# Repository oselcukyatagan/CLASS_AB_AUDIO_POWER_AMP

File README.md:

# CLASS_AB_AUDIO_POWER_AMP

This is the repository for the developing of the class AB audio power amplifier device. 

The repository contains the LTspice and KiCad files along with screenshots of the schematics and simulation results.

Used the technique of making a non polarized cap from 2 polarized electrolytic capacitors. to get the same capacitance, use 2 capacitors thats double the capacitance.

Vbe multiplier and the output stage transistors should be on the same heatsink for thermal considerations.

Ensured the isolated clean ground and dirty ground paths only intersect at a single point at the main power supply socket to prevent ground loops.

Adjust the vbe multiplier trimpot before initial power-on to prevent thermal runaway. calibrated quiescent current only after letting the amplifier idle to reach operating temperature.

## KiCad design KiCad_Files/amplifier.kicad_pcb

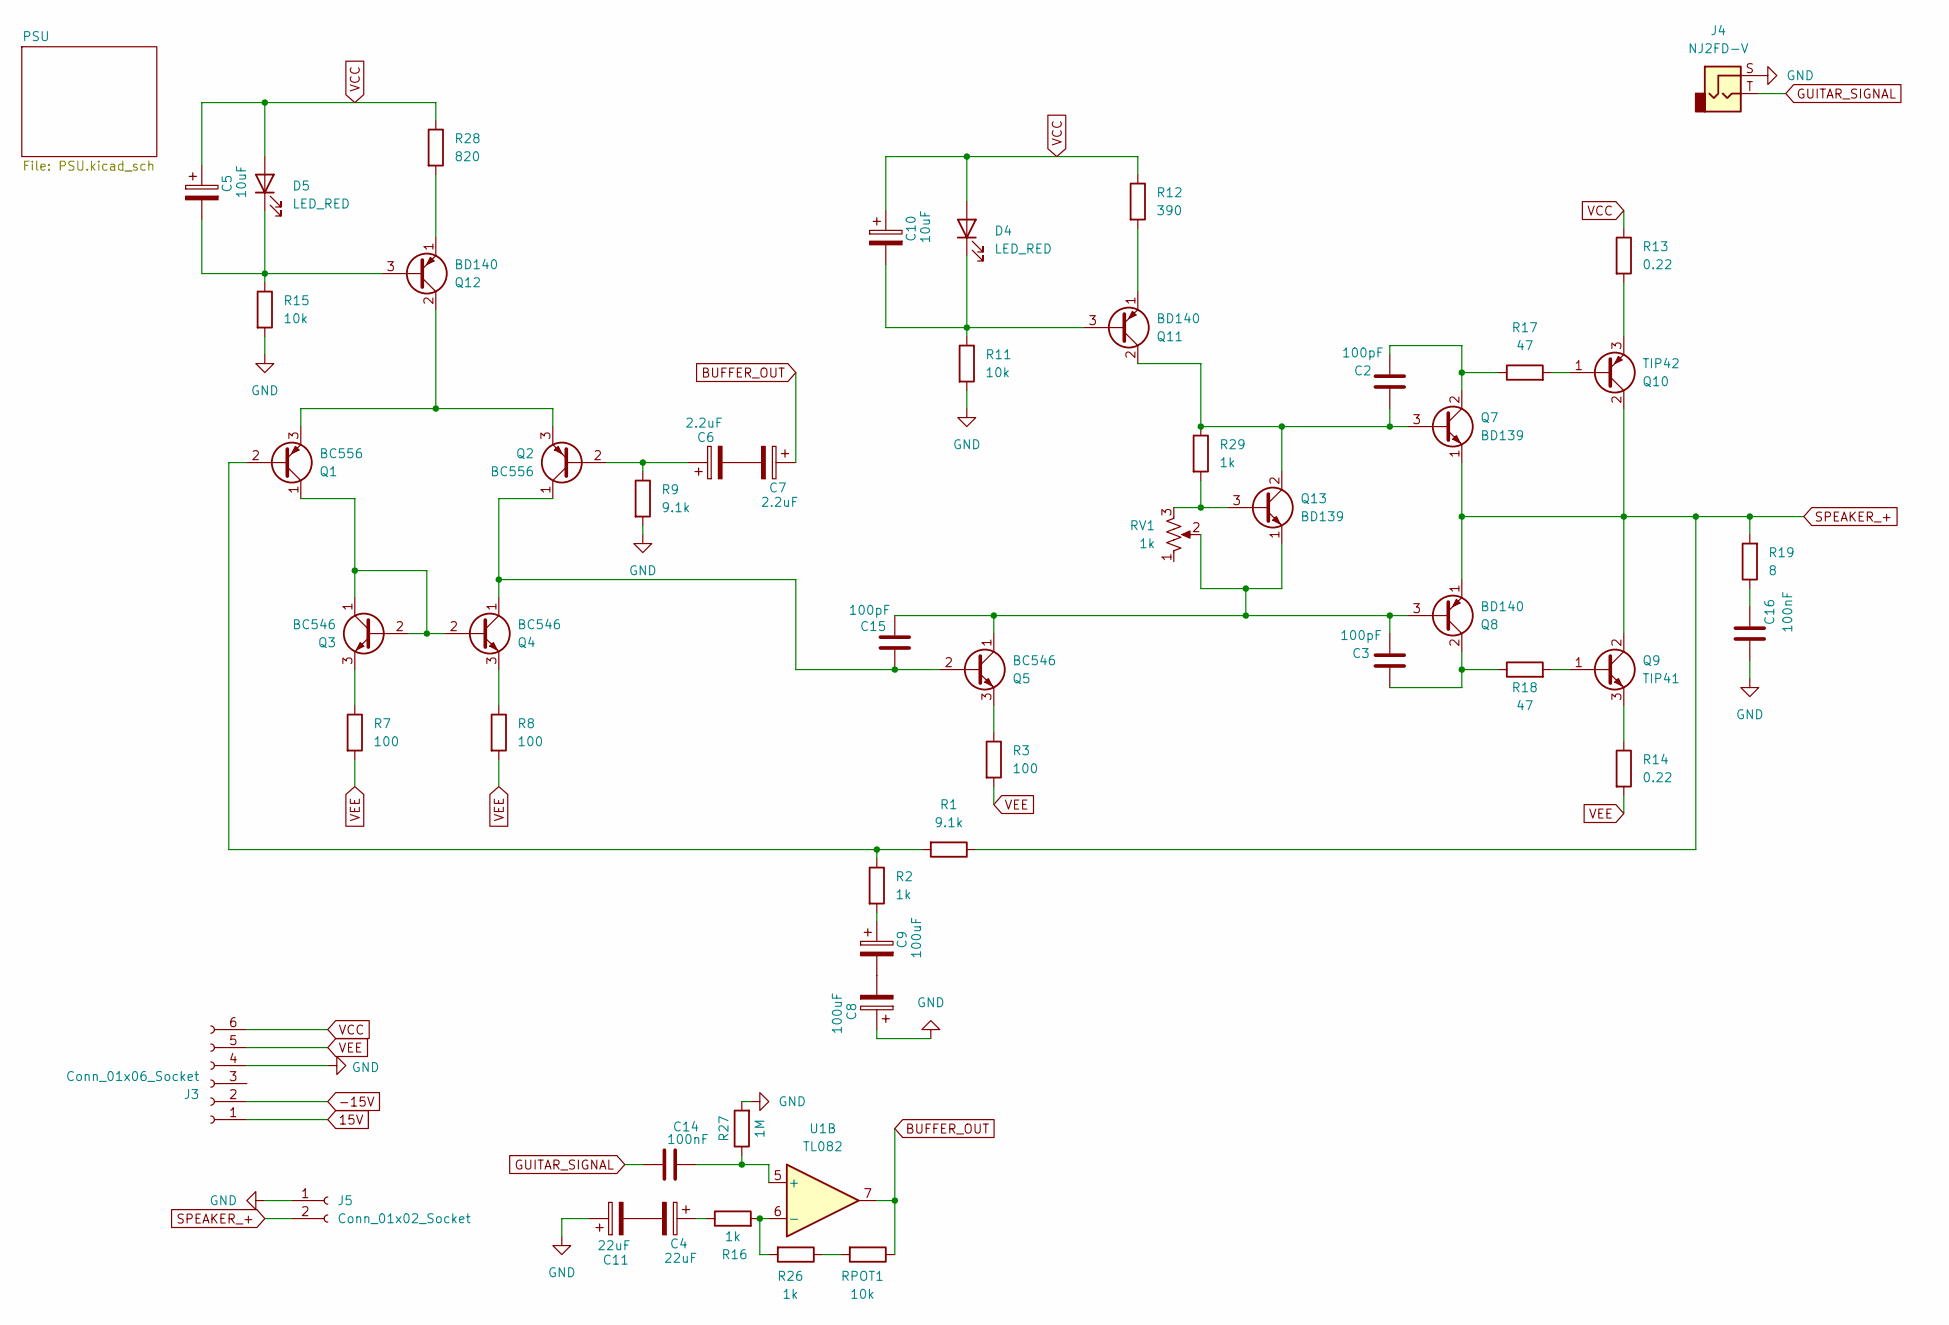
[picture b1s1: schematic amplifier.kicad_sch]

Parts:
C2, C3, C15: 100pF; C_Disc_D5.0mm_W2.5mm_P2.50mm
C4, C11: 22uF; CP_Radial_D8.0mm_P5.00mm
C5, C10: 10uF; CP_Radial_D8.0mm_P5.00mm
C6, C7: 2.2uF; CP_Radial_D8.0mm_P5.00mm
C8, C9: 100uF; CP_Radial_D8.0mm_P5.00mm
C14, C16: 100nF; C_Disc_D5.0mm_W2.5mm_P2.50mm
D4, D5: LED_RED; LED_D4.0mm
J3: Conn_01x06_Socket; TerminalBlock_Phoenix_MKDS-1,5-6-5.08_1x06_P5.08mm_Horizont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
J4: NJ2FD-V; Jack_3.5mm_CUI_SJ-3523-SMT_Horizontal
J5: Conn_01x02_Socket; TerminalBlock_Phoenix_MKDS-1,5-2-5.08_1x02_P5.08mm_Horizont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
Q1, Q2: BC556; TO-92_Inline
Q3, Q4, Q5: BC546; TO-92_Inline
Q7, Q13: BD139; TO-126-3_Vertical
Q8, Q11, Q12: BD140; TO-126-3_Vertical
Q9: TIP41; TO-220-3_Vertical
Q10: TIP42; TO-220-3_Vertical
R1, R9: 9.1k; R_Axial_DIN0207_L6.3mm_D2.5mm_P10.16mm_Horizontal
R2, R16, R26, R29: 1k; R_Axial_DIN0207_L6.3mm_D2.5mm_P10.16mm_Horizontal
R3, R7, R8: 100; R_Axial_DIN0207_L6.3mm_D2.5mm_P10.16mm_Horizontal
R11, R15: 10k; R_Axial_DIN0207_L6.3mm_D2.5mm_P10.16mm_Horizontal
R12: 390; R_Axial_DIN0207_L6.3mm_D2.5mm_P10.16mm_Horizontal
R13, R14: 0.22; R_Axial_DIN0207_L6.3mm_D2.5mm_P10.16mm_Horizontal
R17, R18: 47; R_Axial_DIN0207_L6.3mm_D2.5mm_P10.16mm_Horizontal
R19: 8; R_Axial_DIN0207_L6.3mm_D2.5mm_P10.16mm_Horizontal
R27: 1M; R_Axial_DIN0207_L6.3mm_D2.5mm_P10.16mm_Horizontal
R28: 820; R_Axial_DIN0207_L6.3mm_D2.5mm_P10.16mm_Horizontal
RPOT1: 10k; Potentiometer_ACP_CA6-H2,5_Horizontal
RV1: 1k; Potentiometer_ACP_CA6-H2,5_Horizontal
U1: TL082; DIP-8_W7.62mm

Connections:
15V: J3.1; also elsewhere on the board
-15V: J3.2; also elsewhere on the board
BUFFER_OUT: C7.1, RPOT1.1, U1.7
GUITAR_SIGNAL: C14.1, J4.T
unnamed: C4.1, R16.1
unnamed: C6.2, C7.2
unnamed: C8.2, C9.2
unnamed: C9.1, R2.2
unnamed: C4.2, C11.2
unnamed: C16.2, R19.1
unnamed: C10.2, D4.1 (K), Q11.3 (B), R11.1
unnamed: C5.2, D5.1 (K), Q12.3 (B), R15.1
unnamed: Q1.2 (B), R1.2, R2.1
unnamed: Q1.1 (C), Q3.1 (C), Q3.2 (B), Q4.2 (B)
unnamed 20: Q1.3 (E), Q2.3 (E), Q12.2 (C); also elsewhere on the board
unnamed: C6.1, Q2.2 (B), R9.1
unnamed: C15.1, Q2.1 (C), Q4.1 (C), Q5.2 (B)
unnamed: Q3.3 (E), R7.1
unnamed: Q4.3 (E), R8.1
unnamed: Q5.3 (E), R3.1
unnamed: C2.2, Q7.2 (C), R17.1
unnamed: C3.1, Q8.2 (C), R18.1
unnamed: Q9.1 (B), R18.2
unnamed: Q9.3 (E), R14.1
unnamed: Q10.1 (B), R17.2
unnamed: Q10.3 (E), R13.2
unnamed: C2.1, Q7.3 (B), Q11.2 (C), Q13.2 (C), R29.1
unnamed: Q11.1 (E), R12.2
unnamed: Q12.1 (E), R28.2
unnamed: Q13.3 (B), R29.2, RV1.3
unnamed: C3.2, C15.2, Q5.1 (C), Q8.3 (B), Q13.1 (E), RV1.2
unnamed: R26.1, RPOT1.2
unnamed: C14.2, R27.1, U1.5 (+)
unnamed: R16.2, R26.2, U1.6 (-)
SPEAKER_+: J5.2, Q7.1 (E), Q8.1 (E), Q9.2 (C), Q10.2 (C), R1.1, R19.2
TRANSFORMER_0V: C8.1, C11.1, C16.1, J3.4, J4.S, J5.1, R9.2, R11.2, R15.2, R27.2; also elsewhere on the board
VCC: C5.1, C10.1, D4.2 (A), D5.2 (A), J3.6, R12.1, R13.1, R28.1; also elsewhere on the board
VEE: J3.5, R3.2, R7.2, R8.2, R14.2; also elsewhere on the board

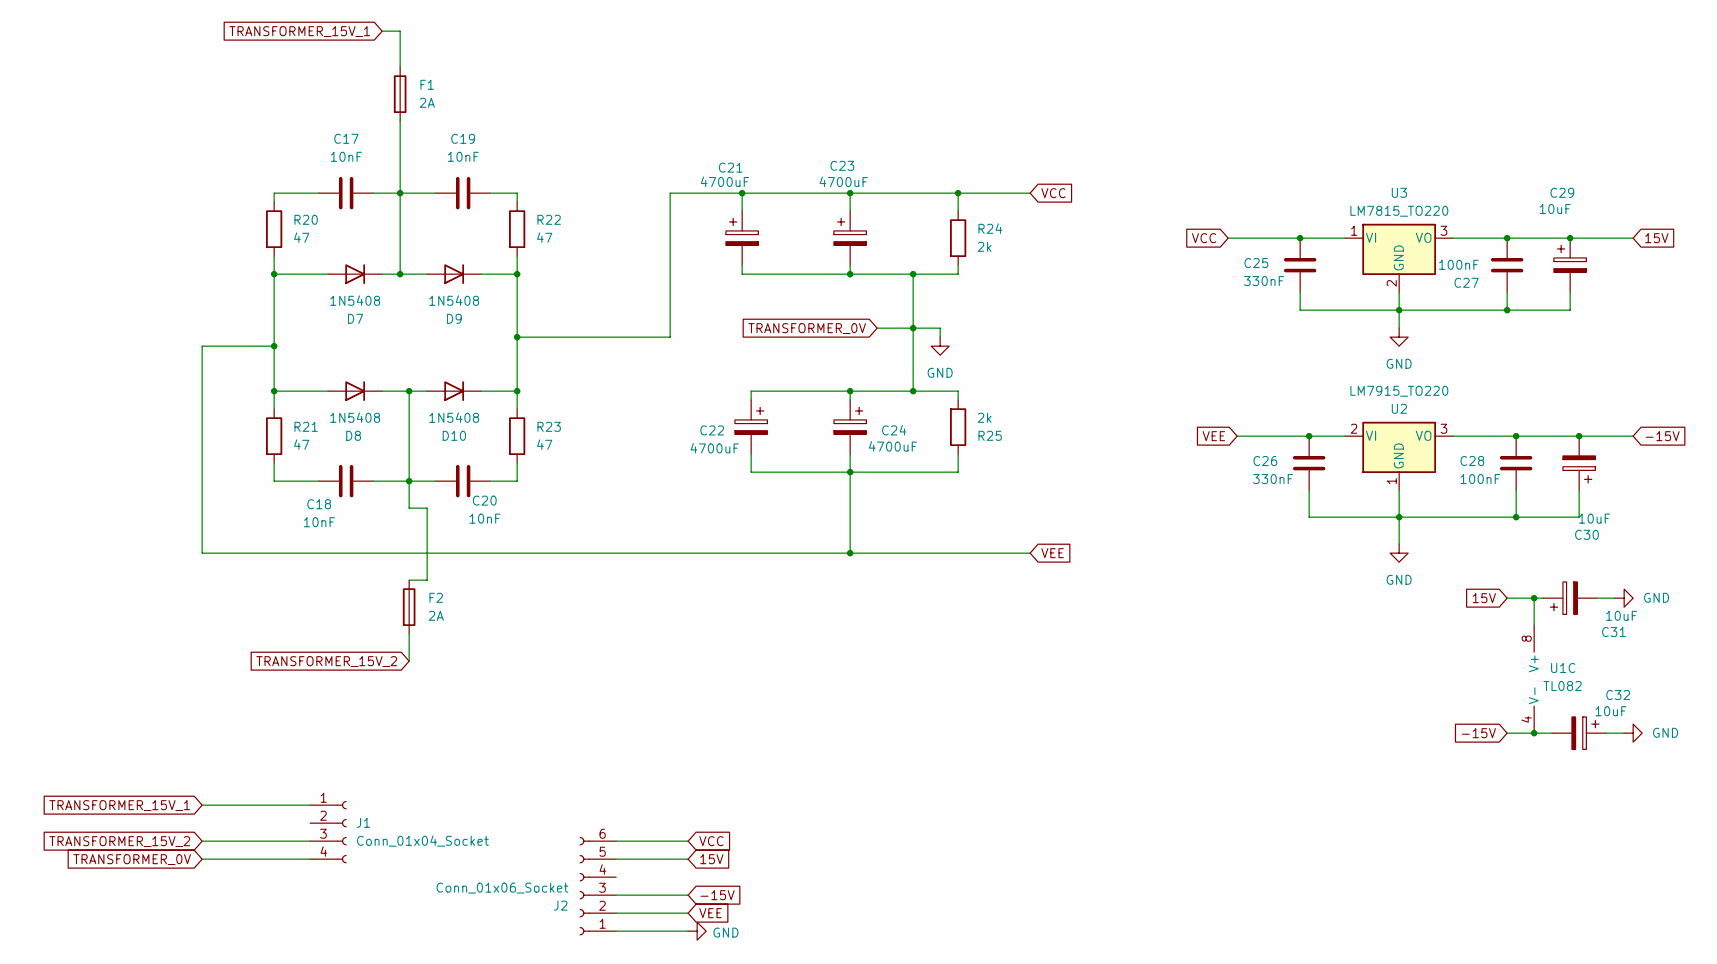
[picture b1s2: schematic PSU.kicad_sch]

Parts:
C17, C18, C19, C20: 10nF; C_Disc_D5.0mm_W2.5mm_P2.50mm
C21, C22, C23, C24: 4700uF; CP_Radial_D16.0mm_P7.50mm
C25, C26: 330nF; C_Rect_L7.2mm_W3.5mm_P5.00mm
C27, C28: 100nF; C_Disc_D5.0mm_W2.5mm_P2.50mm
C29, C30, C31, C32: 10uF; CP_Radial_D8.0mm_P5.00mm
D7, D8, D9, D10: 1N5408; D_DO-201AD_P15.24mm_Horizontal
F1, F2: 2A; Fuseholder_Cylinder-5x20mm_Schurter_0031_8201_Horizontal_Op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
J1: Conn_01x04_Socket; TerminalBlock_Phoenix_MKDS-1,5-4-5.08_1x04_P5.08mm_Horizont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
J2: Conn_01x06_Socket; TerminalBlock_Phoenix_MKDS-1,5-6-5.08_1x06_P5.08mm_Horizont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
R20, R21, R22, R23: 47; R_Axial_DIN0207_L6.3mm_D2.5mm_P10.16mm_Horizontal
R24, R25: 2k; R_Axial_DIN0414_L11.9mm_D4.5mm_P15.24mm_Horizontal
U1: TL082; DIP-8_W7.62mm
U2: LM7915_TO220; TO-220-3_Vertical
U3: LM7815_TO220; TO-220-3_Vertical

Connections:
15V: C27.2, C29.1, C31.1, J2.5, U1.8 (V+), U3.3 (VO); also elsewhere on the board
-15V: C28.1, C30.2, C32.2, J2.3, U1.4 (V-), U2.3 (VO); also elsewhere on the board
unnamed: C17.1, R20.1
unnamed: C18.1, R21.2
unnamed: C19.2, R22.1
unnamed: C20.2, R23.2
unnamed: C17.2, C19.1, D7.1 (K), D9.2 (A), F1.2
unnamed: C18.2, C20.1, D8.1 (K), D10.2 (A), F2.1
TRANSFORMER_0V: C21.2, C22.1, C23.2, C24.1, C25.2, C26.2, C27.1, C28.2, C29.2, C30.1, C31.2, C32.1, J1.4, J2.1, R24.2, R25.2, U2.1 (GND), U3.2 (GND); also elsewhere on the board
TRANSFORMER_15V_1: F1.1, J1.1
TRANSFORMER_15V_2: F2.2, J1.3
VCC: C21.1, C23.1, C25.1, D9.1 (K), D10.1 (K), J2.6, R22.2, R23.1, R24.1, U3.1 (VI); also elsewhere on the board
VEE: C22.2, C24.2, C26.1, D7.2 (A), D8.2 (A), J2.2, R20.2, R21.1, R25.1, U2.2 (VI); also elsewhere on the board

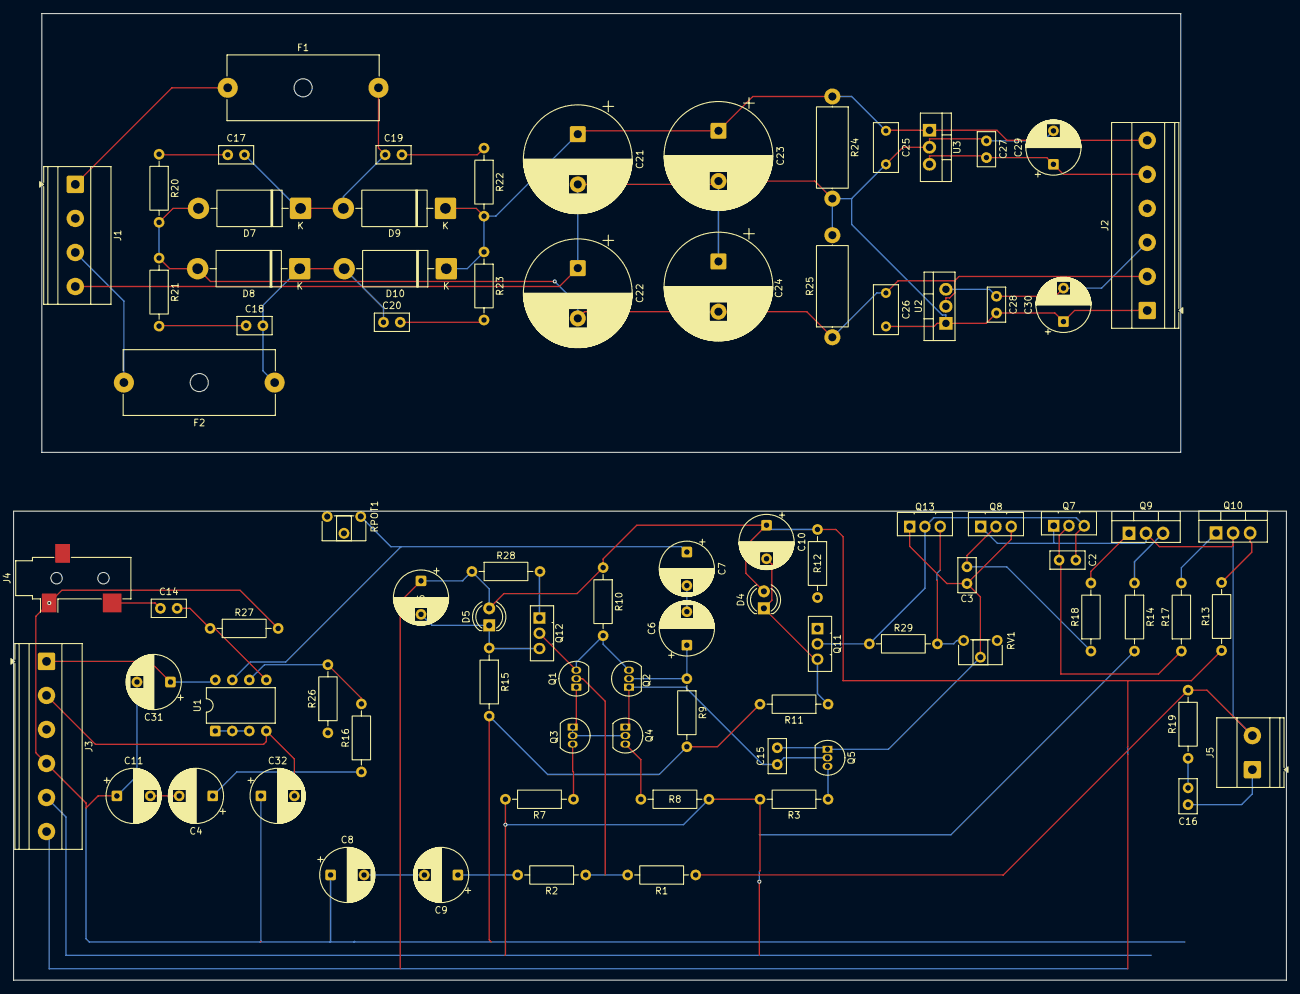
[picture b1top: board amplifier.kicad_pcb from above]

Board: 2 copper layers, 190.0 x 144.3 mm, 85 parts (0 on the bottom side), 46 nets.

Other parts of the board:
R10: 10k; R_Axial_DIN0207_L6.3mm_D2.5mm_P10.16mm_Horizontal

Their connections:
unnamed 20: R10.2; also elsewhere on the board
VCC: R10.1; also elsewhere on the board
